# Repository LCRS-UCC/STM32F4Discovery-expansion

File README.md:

Placa de expansión para el kit STM32F4-Discovery
================================================

Esta es una placa con el propósito de agregar muchos periféricos para poder utilizar el kit de evaluación STM32F4-Discovery.

Periféricos:

* Ethernet
* Mirco-SD
* RGB
* Potenciómetro
* puerto serie con conversor USB
* VGA
* 4 pulsadores 
* 8 leds

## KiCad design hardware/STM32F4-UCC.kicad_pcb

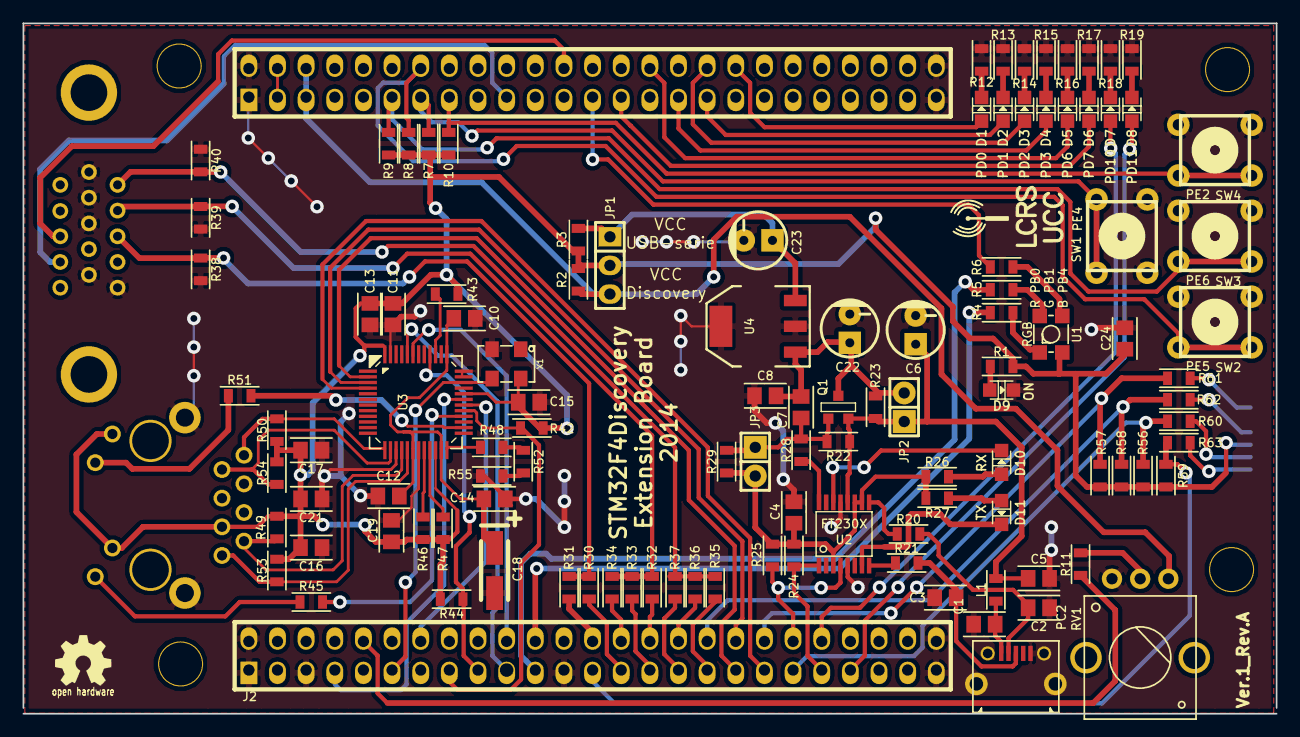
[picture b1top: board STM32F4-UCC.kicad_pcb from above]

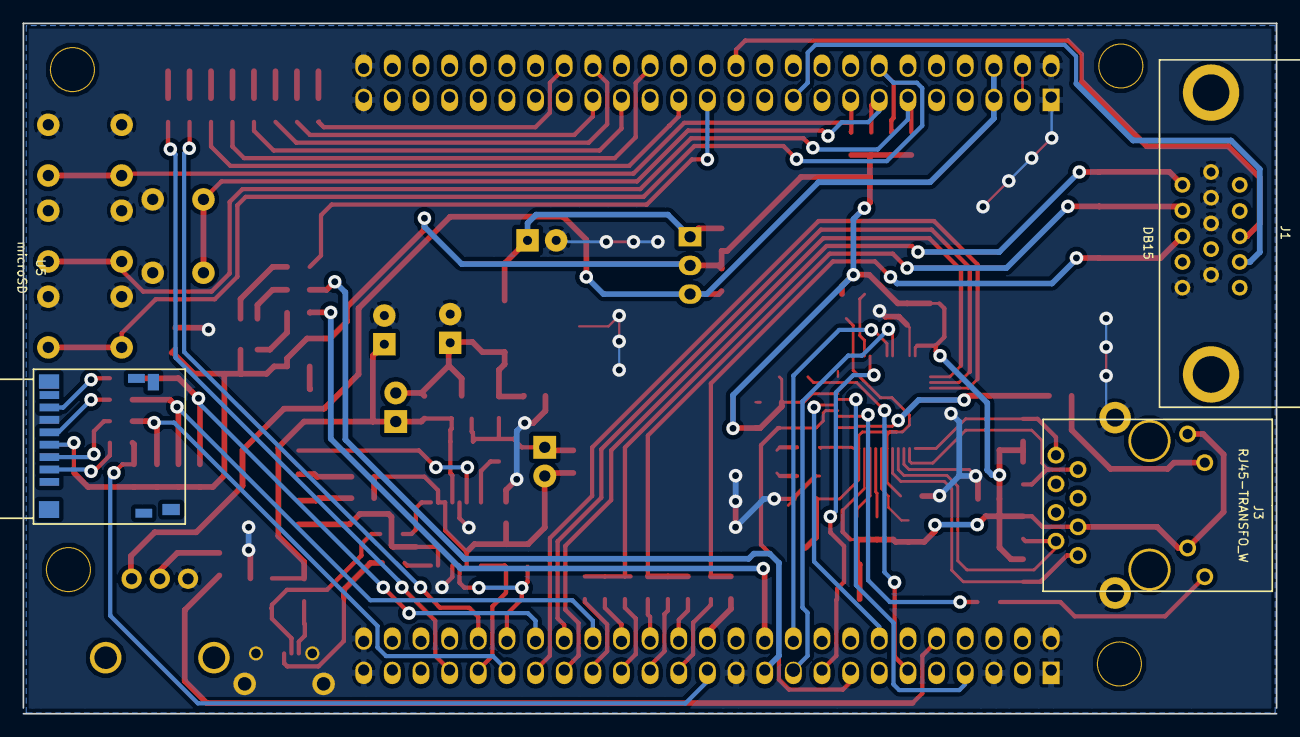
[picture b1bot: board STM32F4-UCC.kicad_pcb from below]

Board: 2 copper layers, 111.1 x 61.2 mm, 119 parts (3 on the bottom side), 96 nets.

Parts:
C1: 10nf; c_0805
C2, C3: 47pF; c_0805
C4, C5, C7, C8, C10, C11, C12, C13, C14, C15, C16, C17, C19, C21, C24: 100nF; c_0805
C6, C22: 4.7uF; Capacitor5x11RM2.5
C18: 10uF (tantalio); TantalC_SizeA_EIA-3216_HandSoldering
C23: 1uF; Capacitor5x11RM2.5
D1: PD0; Led_0805
D2: PD1; Led_0805
D3: PD2; Led_0805
D4: PD3; Led_0805
D5: PD6; Led_0805
D6: PD7; Led_0805
D7: PD10; Led_0805
D8: PD11; Led_0805
D9: ON; Led_0805
D10: RX; Led_0805
D11: TX; Led_0805
J1: DB15; DB_15F-VGA
J2: STM32F4_Discovery_Header; stm32f4_discovery_header
J3: RJ45-TRANSFO_W; RJ45
JP1: Alimentacion; Pin_Header_Straight_1x03
JP2: Alim Ext; Pin_Header_Straight_1x02
JP3: G_MOS; Pin_Header_Straight_1x02
L1: MI0805K601R-10; R_0805
MH: MountingHole_3-5mm_RevA_Date21Jun2010; MountingHole_3-5mm
MH#2, MH#3, MH#4: MountingHole_3-5mm_RevA_Date21Jun2010; MountingHole_3-5mm
Q1: IRLML6402; SOT-23-GDS
R1, R4, R5, R6, R11, R12, R13, R14, R15, R16, R17, R18, R19, R26, R27, R45, R51: 330; R_0805
R2, R3, R23, R29: 0; R_0805
R7, R8, R9, R10, R24, R25, R42: 10k; R_0805
R20, R21: 27; R_0805
R22: 100k; R_0805
R28: 1k; R_0805
R30, R32, R35: 240; R_0805
R31: 470; R_0805
R33, R36: 560; R_0805
R34, R37: 1100; R_0805
R38, R39, R40, R52: 150; R_0805
R43, R44, R46, R47: 2.2k; R_0805
R48: 4.7k; R_0805
R49, R50, R53, R54, R55: 18; R_0805
R56, R57, R58, R59: 47K; R_0805
R60, R61, R62, R63: 22; R_0805
RV1: PC2; POTE
SW1: PE4; PCB_PUSH
SW2: PE5; PCB_PUSH
SW3: PE6; PCB_PUSH
SW4: PE2; PCB_PUSH
U1: RGB; PLCC4
U2: FT230X; SSOP-16
U3: DP83848C; lqfp48
U4: MCP1825S-3302E; SOT-223
U5: microSD
USB-Serie1: USB-MINI-B; Micro_USB_type_B
X1: 50Mhz; crystal_fa128

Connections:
+3.3V: C11.1, C13.1, C15.1, C16.1, C17.1, C19.1, C21.1, C24.1, J3.L1, J3.L3, J3.R3, JP1.2, R1.2, R2.1, R3.1, R7.2, R8.2, R9.2, R10.2, R42.2, R43.2, R44.2, R46.1, R47.1, R49.1, R50.1, R53.2, R54.2, R56.2, R57.2, R58.2, R59.2, U1.2, U3.22, U3.32, U3.48, U5.4, X1.4
+5V: J2.97, J2.98
/3.3V_discovery: J2.95, J2.96, JP1.3, R2.2, RV1.1
/Ethernet/CRS_DV: J2.17, R44.1, U3.40
/Ethernet/MDC: J2.7, U3.31
/Ethernet/MDIO: J2.14, U3.30
/Ethernet/NRST: J2.15, R42.1, U3.29
/Ethernet/OSCIN: J2.11, U3.34, X1.3
/Ethernet/RXD0: J2.20, U3.43
/Ethernet/RXD1: J2.19, U3.44
/Ethernet/TXD0: J2.36, U3.3
/Ethernet/TXD1: J2.37, U3.4
/Ethernet/TX_EN: J2.35, U3.2
/Fuente/3.3V_OUT: C23.1, JP1.1, R3.2, U4.3
/PB0: J2.22, R4.2
/PB1: J2.21, R5.1
/PB4: J2.75, R6.1
/PC2: J2.10, R11.1
/PD0: D1.1, J2.66
/PD1: D2.1, J2.67
/PD2: D3.1, J2.68
/PD3: D4.1, J2.69
/PD6: D5.1, J2.72
/PD7: D6.1, J2.73
/PD10: D7.1, J2.42
/PD11: D8.1, J2.43
/PE2: J2.85, R10.1, SW4.1, SW4.3
/PE4: J2.87, R7.1, SW1.1, SW1.3
/PE5: J2.88, R8.1, SW2.1, SW2.3
/PE6: J2.89, R9.1, SW3.1, SW3.3
/SD-Card/CLK/SCK: J2.34, R58.1, R62.2
/SD-Card/CMD/MOSI: J2.39, R56.1, R60.2
/SD-Card/Dat0/MISO: J2.38, R57.1, R61.2
/SD-Card/Dat3/CS: J2.25, R59.1, R63.2
/USB-Serie/3.3v_FT: C4.1, JP3.2, R24.1, R25.1, R26.1, R27.1, R29.1, U2.3, U2.10, U2.11
/USB-Serie/5v_USB: C7.1, C8.1, C22.1, JP2.2, Q1.D, R23.1, U4.1
/USB-Serie/RX: J2.40, R25.2, U2.4
/USB-Serie/TX: J2.41, R24.2, U2.1
/VGA/VGA_B0: J2.26, R31.2
/VGA/VGA_B1: J2.27, R30.2
/VGA/VGA_G0: J2.28, R34.2
/VGA/VGA_G1: J2.29, R33.2
/VGA/VGA_G2: J2.30, R32.2
/VGA/VGA_HS: J1.13, J2.78
/VGA/VGA_R0: J2.31, R37.2
/VGA/VGA_R1: J2.32, R36.2
/VGA/VGA_R2: J2.33, R35.2
/VGA/VGA_VS: J1.14, J2.81
GND: C1.2, C2.2, C3.2, C4.2, C5.2, C6.2, C8.2, C10.2, C11.2, C12.2, C13.2, C14.2, C15.2, C16.2, C17.2, C18.2, C19.2, C21.2, C22.2, C23.2, C24.2, D9.2, J1.5, J1.6, J1.7, J1.8, J1.10, J2.1, J2.2, J2.5, J2.23, J2.49, J2.50, J2.51, J2.52, J2.99, J2.100, J3.SH, R12.1, R13.1, R14.1, R15.1, R16.1, R17.1, R18.1, R19.1, R38.2, R39.2, R40.2, R55.1, RV1.3, SW1.2, SW1.4, SW2.2, SW2.4, SW3.2, SW3.4, SW4.2, SW4.4, U2.5, U2.13, U3.15, U3.19, U3.35, U3.36, U3.47, U4.2, U4.4, U5.6, USB-Serie1.5, USB-Serie1.6, USB-Serie1.7, USB-Serie1.8, USB-Serie1.9, X1.2
unnamed: C1.1, L1.1, USB-Serie1.1
unnamed: C2.1, R20.2, USB-Serie1.2
unnamed: C3.1, R21.2, USB-Serie1.3
unnamed: C5.1, C6.1, JP2.1, L1.2, Q1.S, R22.1, R23.2, U2.12
unnamed: C7.2, JP3.1, Q1.G, R22.2, R28.2, R29.2
unnamed: C10.1, C12.1, C14.1, C18.1, U3.18, U3.23, U3.37
unnamed: D1.2, R12.2
unnamed: D2.2, R13.2
unnamed: D3.2, R14.2
unnamed: D4.2, R15.2
unnamed: D5.2, R16.2
unnamed: D6.2, R17.2
unnamed: D7.2, R18.2
unnamed: D8.2, R19.2
unnamed: D9.1, R1.1
unnamed: D10.1, R26.2
unnamed: D10.2, U2.14
unnamed: D11.1, R27.2
unnamed: D11.2, U2.7
unnamed: J1.1, R35.1, R36.1, R37.1, R40.1
unnamed: J1.2, R32.1, R33.1, R34.1, R39.1
unnamed: J1.3, R30.1, R31.1, R38.1
unnamed: J3.L2, R51.1
unnamed: J3.L4, R45.1
unnamed: J3.R1, R53.1, U3.17
unnamed: J3.R2, R49.2, U3.16
unnamed: J3.R7, R54.1, U3.14
unnamed: J3.R8, R50.2, U3.13
unnamed: R4.1, U1.1
unnamed: R5.2, U1.4
unnamed: R6.2, U1.3
unnamed: R11.2, RV1.2
unnamed: R20.1, U2.9
unnamed: R21.1, U2.8
unnamed: R28.1, U2.16
unnamed: R43.1, U3.39
unnamed: R45.2, U3.28
unnamed: R46.2, U3.20
unnamed: R47.2, U3.21
unnamed: R48.1, R52.2
unnamed: R48.2, U3.24
unnamed: R51.2, U3.26
unnamed: R52.1, R55.2
unnamed: R60.1, U5.3
unnamed: R61.1, U5.7
unnamed: R62.1, U5.5
unnamed: R63.1, U5.2

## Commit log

2014-06-05 Primeras lineas del esquematico y la placa
2014-06-08 Agregado modulo Ethernet
2014-06-09 added some resistors values
2014-07-28 Se agrego alimentacion por USB-Serie, falta fuente
2014-08-05 Se agrego SD, se colocaron pins en varios modulos, se corrigio orden del VGA
2014-08-09 Arreglada la distribucion de pines
2014-08-14 Terminado el esquematico, iniciado el PCB
2014-08-18 Terminado el Routeo de la Placa
2014-08-20 Se arreglo pista a via
2014-08-22 Se reRouteo con clearance 12 en general
2014-08-24 Placa terminada, serigrafia verificada, logos agregados
2014-08-26 Se agregan salidas de archivos en PDF y se realizan algunos cambios
2014-08-26 Subido pdf nuevo de la placa
2014-08-26 Cambios minimos y nuevo PDF y gerbers
2014-08-27 Placa con errores solucionados
2014-09-27 Ultimos cambios realizados antes de enviar la placa.
2014-09-27 Se acomodaron los archivos para que quede mas prolijo
2014-09-27 Se agregaron carpeta de footprint y salida en pdf y gerbers
2014-10-01 Se agrego la funcionalidad semihosting al proyecto TP4 para poder recibir y transmitir datos por medio de jtag y una consola
2015-04-15 * License added * renamed some directories * removed firmware folder
2015-04-15 * Agregado Readme para github
